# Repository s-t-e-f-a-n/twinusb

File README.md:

# H₂H³ | Twin USB Host Switch × Triple USB Hub (with OLED Telemetry)

**H₂H³** is a compact, STM32 microcontroller-driven USB 2.0 KVM switch and 3-port hub designed to maintain a clean, clutter-free workspace in modern home offices. It enables two computers to seamlessly share a single set of peripherals—like your keyboard, mouse, and flash drives—while delivering live voltage and current telemetry via an integrated OLED display.

> [!NOTE]
> **Project Status & Contribution:** This project is actively developed. The initial commit delivers roughly 90% of the core KVM switching and telemetry functionality in a fully functional prototype stage.
>
> To bring this project to a 100% polished release, **contributions from the open-source community are highly welcome!** Whether you want to optimize edge-case handling in the C++ firmware, implement new USB HID features, or help refine the documentation—feel free to open an issue or submit a Pull Request. Let's build this together!

* **Smart Break-Before-Make Switching:** Advanced, software-controlled VBUS and data line multiplexing ensures safe, glitch-free transitions and isolated power rails between both host PCs.
* **Integrated 3-Port Hub:** Built-in Genesys Logic controller expands a single shared USB connection into three downstream ports for your everyday desk peripherals.
* **🚀 Native Host-MCU Communication (Endless Use Cases!):** Unlike dumb KVM switches, the onboard STM32 MCU is wired directly into the hub as a **fourth USB peripheral device**. This allows the MCU to communicate natively with the active Host PC—opening up vast possibilities for custom PC desktop apps, background telemetry logging, hardware automation scripts, or even full USB HID keyboard/mouse emulation.
* **Live Telemetry Dashboard:** A crisp, integrated 64x32 pixel OLED display provides real-time insights by showing live bus voltage and precise current draw per port.
* **Ergonomic & Screw-less Enclosure:** Features a clean interface with a discreetly placed rear tactile button to prevent cable snags, all housed in a robust, snap-fit PA12-HP Nylon shell optimized for MJF 3D printing.
* **Modern C++ Firmware:** Driven by a powerful STM32G0 architecture running a modular, object-oriented C++ firmware stack with hardware-level overcurrent protection.

🖼️ Jump straight to the [Photo Gallery](#-photo-gallery).

🏪 **Hardware Available:** Skip the assembly line and grab a fully functional H₂H³ on [Tindie](https://www.tindie.com/products/43013/).

## 🔭 Background & Philosophy

H₂H³ represents a personal exploration into modern decentralized manufacturing and open-source engineering. It blends professional design principles with modern open-source software, AI-collaborative programming to refine the C++ firmware, and on-demand fabrication. The fact that an individual engineer can now prototype industrial-grade hardware using low-volume far-east manufacturing is nothing short of incredible.

To give back to the community, the full design files—spanning schematics, mechanics, and source code—are public domain under MIT and CERN Open Hardware licenses. It is intended strictly for educational use, and community-driven remixes are highly encouraged.

## 🛠️ Design Stack & Toolchain

The hardware, enclosure, and software for H₂H³ were designed using the following tools:

* **KiCad 9.0:** Schematic entry and PCB design for the 4-layer board.
* **FreeCAD 1.0:** 3D modeling of the screw-less, snap-fit two-part enclosure.
* **Firmware Toolchain:** Developed in modern modular C++ utilizing **STM32CubeMX** for hardware abstraction. Out of the box, the repository supports a dual-development workflow—you can build and debug the firmware seamlessly using either **Visual Studio Code (via CMake/Ninja)** or **STM32CubeIDE**, depending on your preferred environment.

---

## 🛠️ Hardware Specification

* **Microcontroller:** ARM Cortex-M0+ 32-bit MCU (STM32G0B1KBU6, 64 MHz, 128 KB Flash, 144 KB RAM), integrated as a 4th peripheral on the hub.
* **USB 2.0 Hub Controller:** Genesys Logic GL852G.
* **Physical Interface:** * 2x USB-A Male (Host 1 / Host 2 connections)
  * 3x USB-A Female (Peripheral downstream ports)
* **Telemetry Sensors:** Continuous dual-host VBUS voltage sensing (enables auto-detection) and triple-peripheral current monitoring.
* **Switching Architecture:** Hybrid automatic/software-controlled VBUS muxer combined with hardware USB data line multiplexers.
* **User Interface:** 64x32 pixel OLED screen, 1x rear tactile switch button, and 1x fully programmable RGB LED (color and brightness).
* **Form Factor:** Ultra-compact desktop footprint (approx. 60 × 20 × 20 mm).

<table border="0" style="border: none; border-collapse: collapse;">
  <tr>
    <td style="border: none; padding: 10px;"></td>
    <td style="border: none; padding: 10px;"></td>
    <td style="border: none; padding: 10px;"></td>
  </tr>
</table>

---

## 💻 Software & Firmware Architecture

The firmware is built using **STM32CubeMX** for hardware abstraction and written in **C/C++**.

### Advanced Features

* **Fully Modularized C/C++:** Source code is designed fully modular in C++ with support from the HAL in C automatically created by STM32CubeMX.
* **Optimized ADC Sampling:** Continuous monitoring of port power states with software-side calibration.
* **Overcurrent Detection:** Peripheral current draw of more than 1.5 A enters fault mode which the device resumes from by user confirmation.
* **UART Debug Console:** Retargeted `printf` over the STM32 USART2 or USB virtual COM port.
* **Binary Programming:** Powering on and holding switch button simultaneously enters the programming mode (STM32CubeProgrammer) which enables programming the ST32 integrated flash without the need for a hardware debugger

---

## 📂 Repository Structure

```text
twinusb/
├── assets/                  # Public media & documentation images
├── enclosure/               # Mechanical 3D CAD design (FreeCAD)
├── firmware/                # Production-ready STM32G0 C/C++ firmware
│   ├── App/                 # Core Application Logic (C++)
│   │   ├── Inc/             # Application Managers (Hub, Display, Sensors, UI)
│   │   └── Src/             # Implementation source code
│   ├── Core/                # Hardware peripheral initialization (ADC, I2C, GPIO)
│   ├── cmake/               # Toolchain configuration profiles
│   ├── Libs/                # Embedded drivers & hardware abstraction libraries
│   │   └── oled_waveshare/  # Low-level 0.49" 64x32 OLED display driver components
│   ├── Middlewares/         # STMicroelectronics USB Device Library stack
│   ├── Startup/             # Microcontroller boot vector assembly code
│   └── USB_Device/          # USB CDC Class configuration and descriptor maps
└── hardware/                # Electronics engineering files (KiCad)
    ├── lib_fp/              # Custom PCB footprint libraries (.pretty)
    └── lib_sch/             # Custom schematic component symbols
```

---

## ⚡ Getting Started & Building the Firmware

### 1. Cloning the Repository

```bash
git clone https://github.com/s-t-e-f-a-n/twinusb.git
cd twinusb

```

This project supports a **dual-development workflow**. You can build the firmware using either **VS Code (via CMake)** or the official **STM32CubeIDE**. Choose the workflow that best fits your environment. You do not need to use STM32CubeMX to build the project from scratch.

---

### Method A: Building with VS Code (Recommended)

This method uses CMake and Ninja/Make. It requires a local ARM GCC toolchain installed on your system.

#### Prerequisites

Ensure you have the following installed and available in your system's `PATH`:

* **ARM GNU Toolchain:** `arm-none-eabi-gcc`
* **Build Tools:** `CMake` and `Ninja` (or `Make`)
* **VS Code Extensions:**
* [CMake Tools](https://marketplace.visualstudio.com/items?itemName=ms-vscode.cmake-tools)
* [C/C++ Extension Pack](https://marketplace.visualstudio.com/items?itemName=ms-vscode.cpptools-extension-pack)

#### VS Code Setup & Build Steps

1. **Open Project:** Open the `firmware` directory in VS Code.
2. **Select Compiler Kit:** Open the Command Palette (`Ctrl+Shift+P` / `Cmd+Shift+P`), search for **`CMake: Select a Kit`**, and select your installed `arm-none-eabi` compiler.
3. **Select Build Variant:** Choose either `Debug` or `Release` from the CMake status bar at the bottom.
4. **Configure Project:** Run **`CMake: Configure`** from the Command Palette. This will clean-room generate your local `build/` directory with the correct absolute paths for your machine.
5. **Compile:** Click **`Build`** in the status bar or press `F7`.

---

### Method B: Building with STM32CubeIDE

STM32CubeIDE is an all-in-one Eclipse-based IDE that includes its own compiler toolchain and internal build system out of the box.

#### STM32CubeIDE Setup & Build Steps

1. **Import Project:**

* Open STM32CubeIDE.
* Go to `File` ➔ `Open Projects from Filesystem...`
* Select `Directory` ➔ `Choose twinusb folder` and click *Select Folder*.
* Click *Finish*.

2. **Index Project:** Wait a few moments for the IDE to finish indexing the source files.

3. **Compile:** Click the **Hammer icon (Build)** in the top toolbar, or press `Ctrl+B` (`Cmd+B` on macOS).

---

### ⚠️ Crucial Note on Code Generation (C++ Integration)

The core application logic of this project is written in modern **C++** and lives inside the `App/` directory (`App/Src` and `App/Inc`), keeping it cleanly decoupled from the autogenerated ST HAL layer.

If you decide to open the `twinusb.stm32.ioc` file to modify pinouts or peripherals via STM32CubeMX and click **"Generate Code"**, the tools will reset the project workspace to ST's default pure-C template.

**If your IDE loses track of the C++ files after code generation, fix it manually:**

* **In STM32CubeIDE:** Right-click the project ➔ `Properties` ➔ `C/C++ General` ➔ `Paths and Symbols`.
* Under **Includes**, re-add the `App/Inc` directory.
* Under **Source Location**, re-add the `App/Src` directory.

* **In VS Code:** Simply run **`CMake: Delete Cache and Reconfigure`** from the Command Palette to force CMake to re-scan the file structure.

---

## 🏭 Sourcing the Hardware

### PCB & Assembly

The schematics and PCB layout are located in the `/hardware` folder, designed in KiCad and optimized for automated assembly (PCBA) via services like JLCPCB.

### Enclosure

Print the shell components located in the `/enclosure` folder. Nylon (SLS/MJF technique) is highly recommended for that professional, textured matte finish and mechanical durability.

---

## 📸 Photo Gallery

| &nbsp; | &nbsp; | &nbsp; |
| :---: | :---: | :---: |
|  |  |  |
|  |  |  |
|  |  |  |
|  |  |  |
|  |  |  |
|  |  |  |
|  |  |  |

---

## ⚖️ License

This project is licensed under different Open Source licenses depending on the component:

* 💻 **Firmware & Software:** Licensed under the [MIT License](firmware/LICENSE)
  *(Permissive, commercial-friendly software license)*
* 🔌 **Hardware (PCB & Schematics):** Licensed under the [CERN-OHL-W v2](hardware/LICENSE)
  *(CERN Open Hardware Licence - Weak Copyleft)*
* 📦 **Enclosure (Mechanical CAD):** Licensed under the [CERN-OHL-W v2](enclosure/LICENSE)
  *(CERN Open Hardware Licence - Weak Copyleft)*

All components are copyrighted © 2026 by **s-t-e-f-a-n** who developed them with ❤️

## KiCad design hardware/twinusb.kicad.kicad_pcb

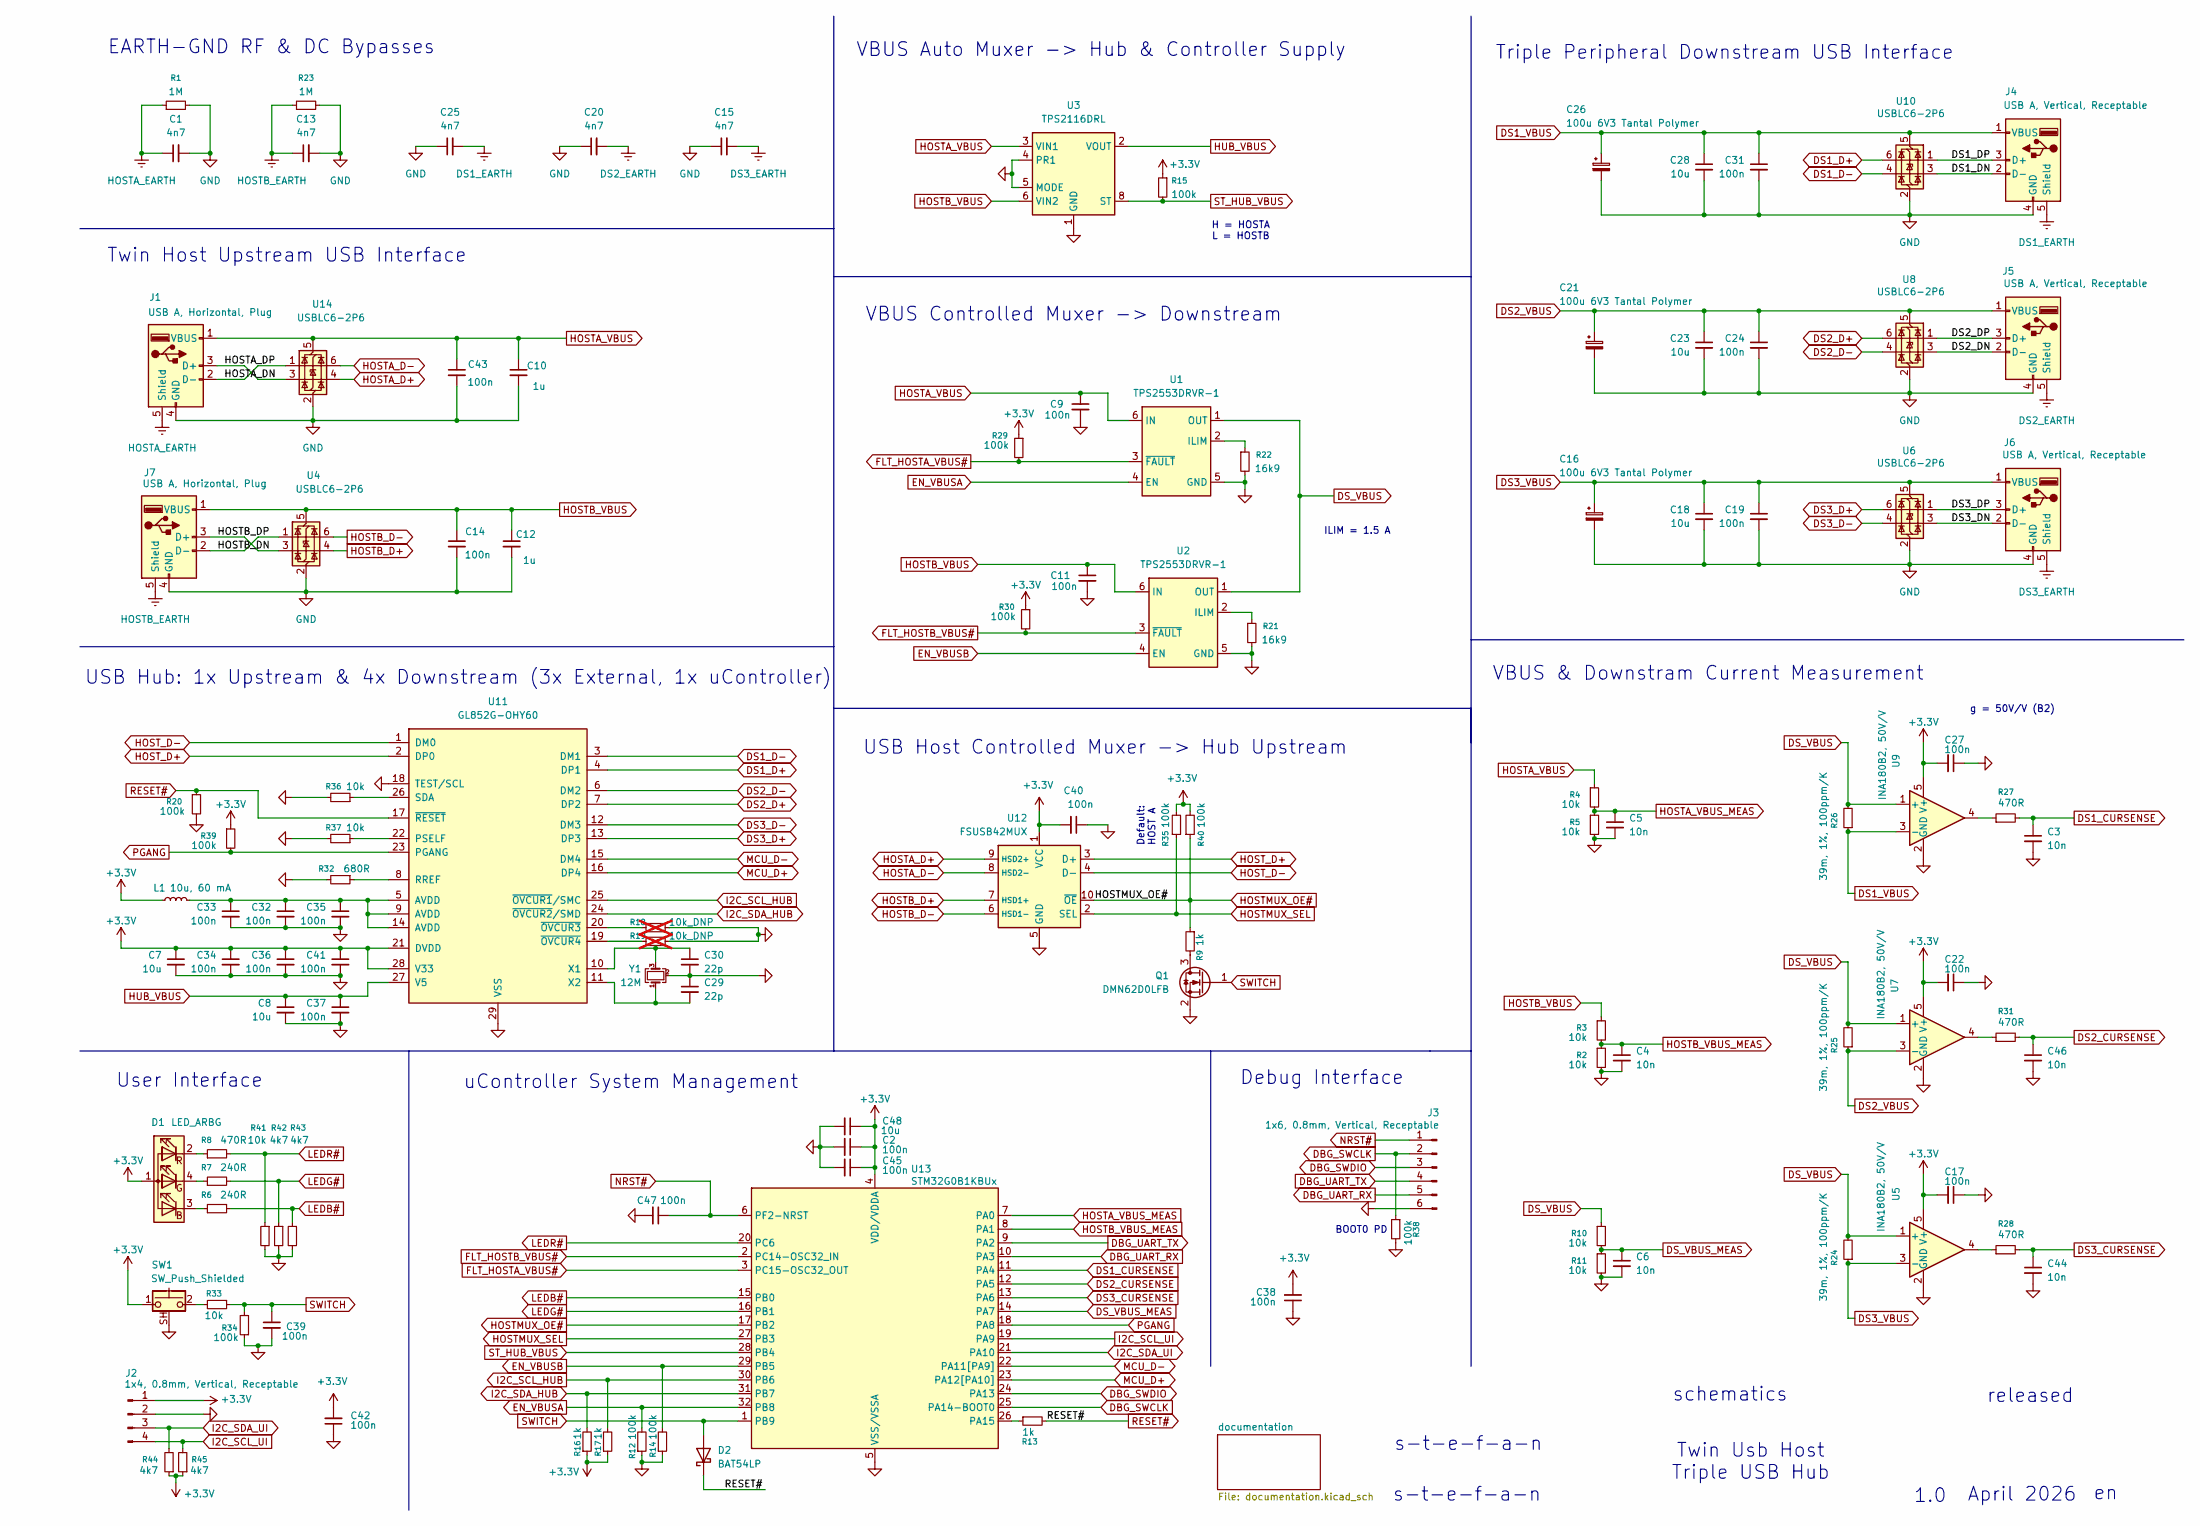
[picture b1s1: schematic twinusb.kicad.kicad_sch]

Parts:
C1, C13, C15, C20, C25: 4n7; C_0603_1608Metric; LCSC PN C85980
C2, C9, C11, C14, C17, C19, C22, C24, C27, C31, C32, C33, C34, C35, C36, C37, C38, C39, C40, C41, C42, C43, C45, C47: 100n; C_0402_1005Metric; LCSC PN C307331
C3, C4, C5, C6, C44, C46: 10n; C_0402_1005Metric; LCSC PN C15195
C7, C8, C18, C23, C28, C48: 10u; C_0603_1608Metric; LCSC PN C19702
C10, C12: 1u; C_0402_1005Metric; LCSC PN C52923
C16, C21, C26: 100u 6V3 Tantal Polymer; CP_EIA-3216-18_Kemet-A; MPN T520A107M006ATE070; LCSC PN C561794
C29, C30: 22p; C_0402_1005Metric; LCSC PN C1555
D1: LED_ARBG; LED_RGB_Kingbright_APHF1608LSEEQBDZGKC; MPN APHF1608LSEEQBDZGKC; LCSC PN C3019171
D2: BAT54LP; Diodes_DFN1006-2; MPN BAT54LP; LCSC PN C134410
J1, J7: USB A, Horizontal, Plug; USB_A_Horizontal_THT; MPN UP2-AH-1-TH; Mouser PN 490-UP2-AH-1-TH
J2: 1x4, 0.8mm, Vertical, Receptable; JST_SUR_BM04B-SURS-TF_1x04-1MP_P0.80mm_Vertical; MPN BM04B-SURS-TF; LCSC PN C495551
J3: 1x6, 0.8mm, Vertical, Receptable; JST_SUR_BM06B-SURS-TF_1x06-1MP_P0.80mm_Vertical; MPN BM06B-SURS-TF; LCSC PN C5118712
J4, J5, J6: USB A, Vertical, Receptable; USB_A_Vertical_AMPHENOL_UE27AE54100; MPN UE27-AE54-100; Mouser PN 523-UE27-AE54-100
L1: 10u, 60 mA; L_0603_1608Metric; MPN MLZ1608N100LTD25; LCSC PN C307750
Q1: DMN62D0LFB; DFN1006-3; MPN DMN62D0LFB; LCSC PN C397945
R1, R23: 1M; R_0402_1005Metric; LCSC PN C26083
R2, R3, R4, R5, R10, R11, R33, R36, R37, R41: 10k; R_0402_1005Metric; LCSC PN C60490
R6, R7: 240R; R_0402_1005Metric; LCSC PN C114755
R8, R27, R28, R31: 470R; R_0402_1005Metric; LCSC PN C25117
R9, R13, R16, R17: 1k; R_0402_1005Metric; LCSC PN C11702
R12, R14, R15, R20, R29, R30, R34, R35, R38, R39, R40: 100k; R_0402_1005Metric; LCSC PN C25741
R18, R19: 10k_DNP; R_0402_1005Metric; LCSC PN C60490; not fitted
R21, R22: 16k9; R_0402_1005Metric; LCSC PN C25858
R24, R25, R26: 39m, 1%, 100ppm/K; R_0603_1608Metric; MPN PE0603FRF7T0R039L; LCSC PN C858571
R32: 680R; R_0402_1005Metric; LCSC PN C25130
R42, R43, R44, R45: 4k7; R_0402_1005Metric; LCSC PN C25900
SW1: SW_Push_Shielded; SW_Tactile_SPST_Angled_PTS645Vx58-2LFS; MPN PTS645VH58-2 LFS; Mouser PN 611-PTS645VH582
U1, U2: TPS2553DRVR-1; WSON-6-1EP_2x2mm_P0.65mm_EP1x1.6mm_ThermalVias; MPN TPS2553DRVR-1; LCSC PN C411878
U3: TPS2116DRL; SOT-583-8; MPN TPS2116DRLR; LCSC PN C3235557
U4, U6, U8, U10, U14: USBLC6-2P6; SOT-666; MPN USBLC6-2P6; LCSC PN C15999
U5, U7, U9: INA180B2, 50V/V; SOT-23-5; MPN INA180B2IDBVR; LCSC PN C2861539
U11: GL852G-OHY60; QFN-28-1EP_5x5mm_P0.5mm_EP3.75x3.75mm_ThermalVias; MPN GL852G-OHY60; LCSC PN C7501404
U12: FSUSB42MUX; MSOP-10_3x3mm_P0.5mm; MPN FSUSB42MUX; LCSC PN C11355
U13: STM32G0B1KBUx; QFN-32-1EP_5x5mm_P0.5mm_EP3.45x3.45mm_ThermalVias; MPN STM32G0B1KBU6; LCSC PN C5159549
Y1: 12M; Crystal_SMD_3225-4Pin_3.2x2.5mm; MPN X322512MSB4SI; LCSC PN C9002

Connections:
+3.3V: C2.1, C7.1, C17.2, C22.2, C27.2, C34.1, C36.1, C38.2, C40.2, C41.1, C42.2, C45.1, C48.1, D1.1 (A), J2.1, L1.1, R15.1, R16.1, R17.1, R29.1, R30.1, R35.2, R39.1, R40.2, R44.1, R45.1, SW1.1, U5.5 (V+), U7.5 (V+), U9.5 (V+), U11.21 (DVDD), U11.28 (V33), U12.1 (VCC), U13.4 (VDD/VDDA)
/DS1_DN: J4.2 (D-), U10.3 (I/O2)
/DS1_DP: J4.3 (D+), U10.1 (I/O1)
/DS2_DN: J5.2 (D-), U8.3 (I/O2)
/DS2_DP: J5.3 (D+), U8.1 (I/O1)
/DS3_DN: J6.2 (D-), U6.3 (I/O2)
/DS3_DP: J6.3 (D+), U6.1 (I/O1)
/HOSTA_DN: J1.2 (D-), U14.1 (I/O1)
/HOSTA_DP: J1.3 (D+), U14.3 (I/O2)
/HOSTB_DN: J7.2 (D-), U4.1 (I/O1)
/HOSTB_DP: J7.3 (D+), U4.3 (I/O2)
DBG_SWCLK: J3.2, R38.1, U13.25 (PA14-BOOT0)
DBG_SWDIO: J3.3, U13.24 (PA13)
DBG_UART_RX: J3.5, U13.10 (PA3)
DBG_UART_TX: J3.4, U13.9 (PA2)
DS1_CURSENSE: C3.1, R27.2, U13.11 (PA4)
DS1_D+: U10.6 (I/O1), U11.4 (DP1)
DS1_D-: U10.4 (I/O2), U11.3 (DM1)
DS1_EARTH: C25.2, J4.5 (Shield)
DS1_VBUS: C26.1, C28.1, C31.1, J4.1 (VBUS), R26.1, U9.3 (-), U10.5 (VBUS)
DS2_CURSENSE: C46.1, R31.2, U13.12 (PA5)
DS2_D+: U8.6 (I/O1), U11.7 (DP2)
DS2_D-: U8.4 (I/O2), U11.6 (DM2)
DS2_EARTH: C20.2, J5.5 (Shield)
DS2_VBUS: C21.1, C23.1, C24.1, J5.1 (VBUS), R25.1, U7.3 (-), U8.5 (VBUS)
DS3_CURSENSE: C44.1, R28.2, U13.13 (PA6)
DS3_D+: U6.6 (I/O1), U11.13 (DP3)
DS3_D-: U6.4 (I/O2), U11.12 (DM3)
DS3_EARTH: C15.2, J6.5 (Shield)
DS3_VBUS: C16.1, C18.1, C19.1, J6.1 (VBUS), R24.1, U5.3 (-), U6.5 (VBUS)
DS_VBUS: R10.1, R24.2, R25.2, R26.2, U1.1 (OUT), U2.1 (OUT), U5.1 (+), U7.1 (+), U9.1 (+)
DS_VBUS_MEAS: C6.1, R10.2, R11.1, U13.14 (PA7)
EN_VBUSA: R12.2, U1.4 (EN), U13.32 (PB8)
EN_VBUSB: R14.2, U2.4 (EN), U13.29 (PB5)
FLT_HOSTA_VBUS#: R29.2, U1.3 (~FAULT), U13.3 (PC15-OSC32_OUT)
FLT_HOSTB_VBUS#: R30.2, U2.3 (~FAULT), U13.2 (PC14-OSC32_IN)
GND: C1.2, C2.2, C3.2, C4.2, C5.2, C6.2, C7.2, C8.2, C9.2, C10.2, C11.2, C12.2, C13.2, C14.2, C15.1, C16.2, C17.1, C18.2, C19.2, C20.1, C21.2, C22.1, C23.2, C24.2, C25.1, C26.2, C27.1, C28.2, C29.1, C30.2, C31.2, C32.2, C33.2, C34.2, C35.2, C36.2, C37.2, C38.1, C39.2, C40.1, C41.2, C42.1, C43.2, C44.2, C45.2, C46.2, C47.2, C48.2, J1.4 (GND), J2.2, J3.6, J4.4 (GND), J5.4 (GND), J6.4 (GND), J7.4 (GND), Q1.2 (S), R1.2, R2.2, R5.2, R11.2, R12.1, R14.1, R18.1, R19.1, R20.2, R21.2, R22.2, R23.2, R32.2, R34.1, R36.2, R37.2, R38.2, R41.2, R42.2, R43.2, SW1.SH (B), U1.5 (GND), U1.7 (TP), U2.5 (GND), U2.7 (TP), U3.1 (GND), U3.4 (PR1), U3.5 (MODE), U4.2 (GND), U5.2 (GND), U6.2 (GND), U7.2 (GND), U8.2 (GND), U9.2 (GND), U10.2 (GND), U11.18 (TEST/SCL), U11.29 (VSS), U12.5 (GND), U13.5 (VSS/VSSA), U13.33 (VSS), U14.2 (GND), Y1.2 (G), Y1.4 (G)
HOSTA_D+: U12.9 (HSD2+), U14.4 (I/O2)
HOSTA_D-: U12.8 (HSD2-), U14.6 (I/O1)
HOSTA_EARTH: C1.1, J1.5 (Shield), R1.1
HOSTA_VBUS: C9.1, C10.1, C43.1, J1.1 (VBUS), R4.1, U1.6 (IN), U3.3 (VIN1), U14.5 (VBUS)
HOSTA_VBUS_MEAS: C5.1, R4.2, R5.1, U13.7 (PA0)
HOSTB_D+: U4.4 (I/O2), U12.7 (HSD1+)
HOSTB_D-: U4.6 (I/O1), U12.6 (HSD1-)
HOSTB_EARTH: C13.1, J7.5 (Shield), R23.1
HOSTB_VBUS: C11.1, C12.1, C14.1, J7.1 (VBUS), R3.1, U2.6 (IN), U3.6 (VIN2), U4.5 (VBUS)
HOSTB_VBUS_MEAS: C4.1, R2.1, R3.2, U13.8 (PA1)
HOSTMUX_OE#: R9.1, R40.1, U12.10 (~OE), U13.17 (PB2)
HOSTMUX_SEL: R35.1, U12.2 (SEL), U13.27 (PB3)
HOST_D+: U11.2 (DP0), U12.3 (D+)
HOST_D-: U11.1 (DM0), U12.4 (D-)
HUB_VBUS: C8.1, C37.1, U3.2 (VOUT), U3.7 (VOUT), U11.27 (V5)
I2C_SCL_HUB: R17.2, U11.25 (~OVCUR1/SMC), U13.30 (PB6)
I2C_SCL_UI: J2.4, R45.2, U13.19 (PA9)
I2C_SDA_HUB: R16.2, U11.24 (~OVCUR2/SMD), U13.31 (PB7)
I2C_SDA_UI: J2.3, R44.2, U13.21 (PA10)
LEDB#: R6.2, R43.1, U13.15 (PB0)
LEDG#: R7.2, R42.1, U13.16 (PB1)
LEDR#: R8.2, R41.1, U13.20 (PC6)
MCU_D+: U11.16 (DP4), U13.23 (PA12[PA10])
MCU_D-: U11.15 (DM4), U13.22 (PA11[PA9])
NRST#: C47.1, J3.1, U13.6 (PF2-NRST)
unnamed: C32.1, C33.1, C35.1, L1.2, U11.5 (AVDD), U11.9 (AVDD), U11.14 (AVDD)
unnamed: D1.3 (BK), R6.1
unnamed: D1.4 (GK), R7.1
unnamed: D1.2 (RK), R8.1
unnamed: Q1.3 (D), R9.2
unnamed: R27.1, U9.4
unnamed: R28.1, U5.4
unnamed: R31.1, U7.4
unnamed: R33.2, SW1.2
unnamed: R22.1, U1.2 (ILIM)
unnamed: R21.1, U2.2 (ILIM)
unnamed: R37.1, U11.22 (PSELF)
unnamed: R32.1, U11.8 (RREF)
unnamed: R36.1, U11.26 (SDA)
unnamed: C30.1, U11.10 (X1), Y1.3
unnamed: C29.2, U11.11 (X2), Y1.1
unnamed: R18.2, U11.20 (~OVCUR3)
unnamed: R19.2, U11.19 (~OVCUR4)
unnamed: R13.1, U13.26 (PA15)
PGANG: R39.2, U11.23 (PGANG), U13.18 (PA8)
RESET#: D2.1 (K), R13.2, R20.1, U11.17 (~RESET)
ST_HUB_VBUS: R15.2, U3.8 (ST), U13.28 (PB4)
SWITCH: C39.1, D2.2 (A), Q1.1 (G), R33.1, R34.2, U13.1 (PB9)

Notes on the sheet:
ILIM = 1.5 A
s-t-e-f-a-n
USB Host Controlled Muxer -> Hub Upstream
Triple Peripheral Downstream USB Interface
1.0
schematics
BOOT0 PD
H = HOSTA L = HOSTB
VBUS & Downstram Current Measurement
VBUS Auto Muxer -> Hub & Controller Supply
April 2026
User Interface
EARTH-GND RF & DC Bypasses
Twin Host Upstream USB Interface
uController System Management
Default: HOST A
Debug Interface
Twin Usb Host Triple USB Hub
USB Hub: 1x Upstream & 4x Downstream (3x External, 1x uController)
VBUS Controlled Muxer -> Downstream
released
g = 50V/V (B2)

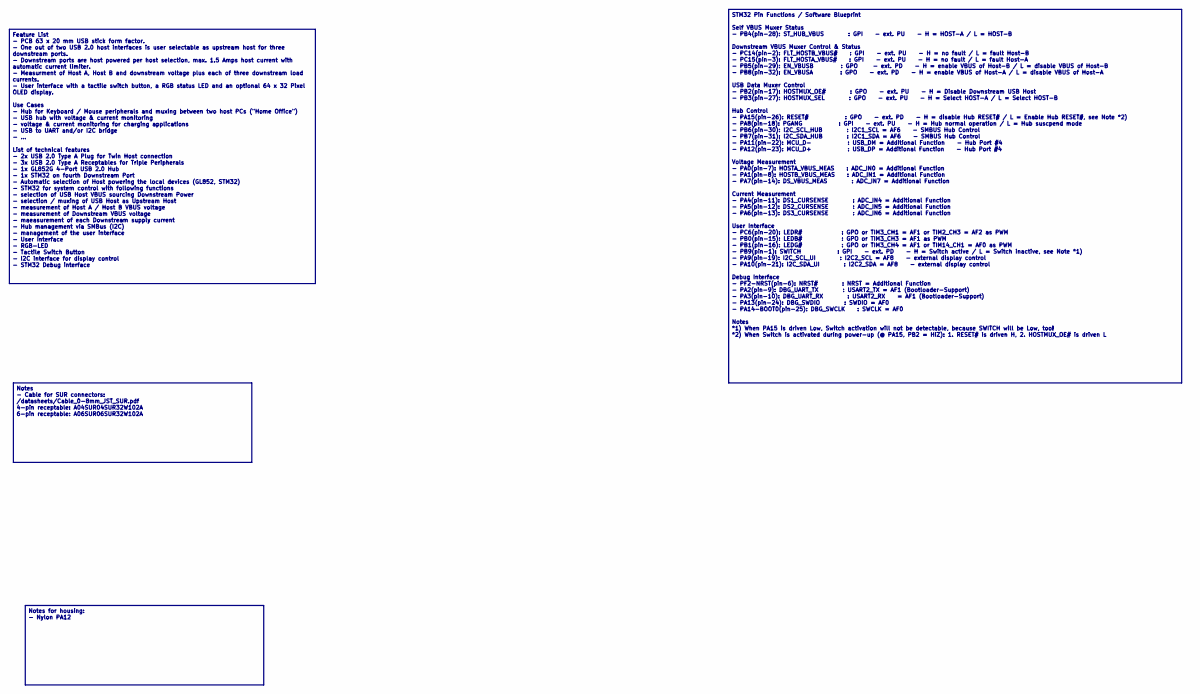
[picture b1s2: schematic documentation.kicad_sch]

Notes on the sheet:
Notes - Cable for SUR connectors: /datasheets/Cable_0-8mm_JST_SUR.pdf 4-pin receptable: A04SUR04SUR32W102A 6-pin receptable: A06SUR06SUR32W102A
STM32 Pin Functions / Software Blueprint Self VBUS Muxer Status - PB4(pin-28): ST_HUB_VBUS : GPI - ext. PU - H = HOST-A / L = HOST-B Downstream VBUS Muxer Control & Status - PC14(pin-2): FLT_HOSTB_VBUS# : GPI - ext. PU - H = no fault / L = fault Host-B - PC15(pin-3): FLT_HOSTA_VBUS# : GPI - ext. PU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
Feature List - PCB 63 x 20 mm USB stick form factor. - One out of two USB 2.0 host interfaces is user selectable as upstream host for three downstream ports. - Downstream ports are host powered per host selection, max. 1.5 Amps host current with automatic current limiter. - Measurment of Host A, Ho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
Notes for housing: - Nylon PA12

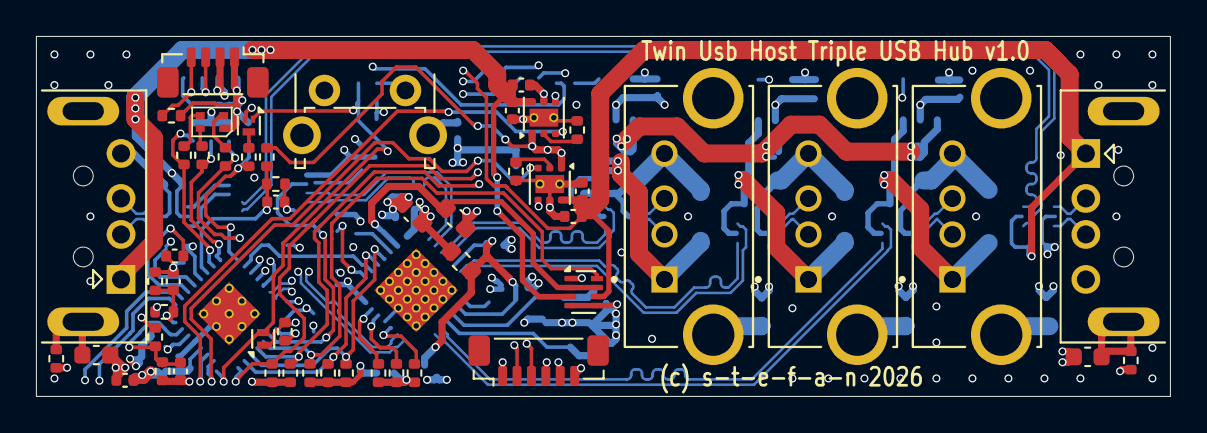
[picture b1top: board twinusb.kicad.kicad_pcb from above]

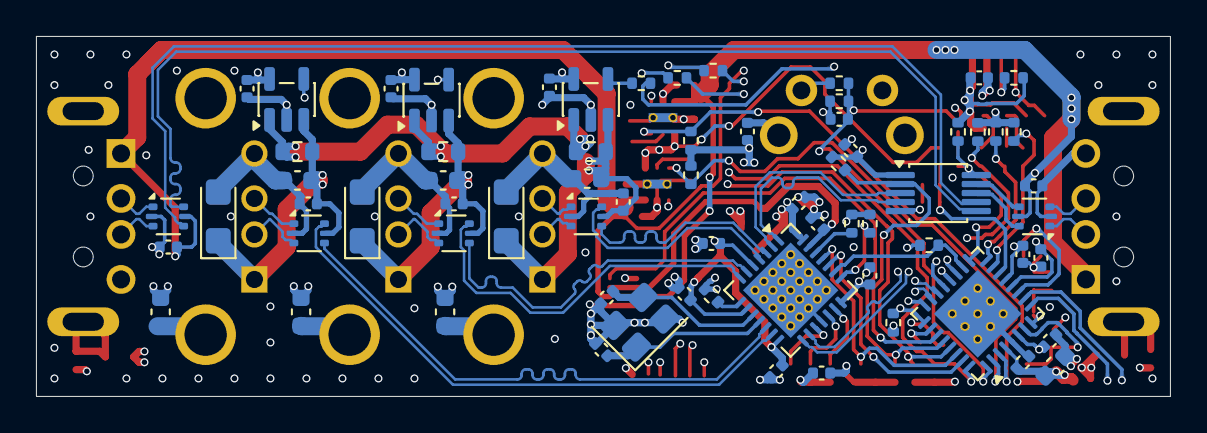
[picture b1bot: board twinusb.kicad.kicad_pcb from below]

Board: 4 copper layers, 63.0 x 20.0 mm, 120 parts (68 on the bottom side), 85 nets.

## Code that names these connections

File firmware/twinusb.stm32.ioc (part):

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Mcu.Name=STM32G0B1K(B-C-E)Ux
Mcu.Package=UFQFPN32
Mcu.UserName=STM32G0B1KBUx
PA0.GPIOParameters=GPIO_Label
PA0.GPIO_Label=HOSTA_VBUS_MEAS
PA0.Mode=IN0
PA0.Signal=ADC1_IN0
PA1.GPIOParameters=GPIO_Label
PA1.GPIO_Label=HOSTB_VBUS_MEAS
PA1.Mode=IN1
PA1.Signal=ADC1_IN1
PA10.GPIOParameters=GPIO_Label
PA10.GPIO_Label=I2C_SDA_UI
PA10.Mode=I2C
PA10.Signal=I2C2_SDA
PA11\ [PA9].GPIOParameters=GPIO_Label
PA11\ [PA9].GPIO_Label=MCU_DM
PA11\ [PA9].Mode=Device
PA11\ [PA9].Signal=USB_DM
PA12\ [PA10].GPIOParameters=GPIO_Label
PA12\ [PA10].GPIO_Label=MCU_DP
PA12\ [PA10].Mode=Device
PA12\ [PA10].Signal=USB_DP
PA13.Mode=Serial_Wire
PA13.Signal=SYS_SWDIO
PA14-BOOT0.Mode=Serial_Wire
PA14-BOOT0.Signal=SYS_SWCLK
PA15.GPIOParameters=GPIO_Label
PA15.GPIO_Label=RESETn
PA15.Signal=GPIO_Output
PA2.Mode=Asynchronous
PA2.Signal=USART2_TX
PA3.Mode=Asynchronous
PA3.Signal=USART2_RX
PA4.GPIOParameters=GPIO_Label
PA4.GPIO_Label=DS1_CURSENSE
PA4.Mode=IN4
PA4.Signal=ADC1_IN4
PA5.GPIOParameters=GPIO_Label
PA5.GPIO_Label=DS2_CURSENSE
PA5.Mode=IN5
PA5.Signal=ADC1_IN5
PA6.GPIOParameters=GPIO_Label
PA6.GPIO_Label=DS3_CURSENSE
PA6.Mode=IN6
PA6.Signal=ADC1_IN6
PA7.GPIOParameters=GPIO_Label
PA7.GPIO_Label=DS_VBUS_MEAS
PA7.Mode=IN7
PA7.Signal=ADC1_IN7
PA8.GPIOParameters=GPIO_Label
PA8.GPIO_Label=PGANG
PA8.Signal=GPIO_Input
PA9.GPIOParameters=GPIO_Label
PA9.GPIO_Label=I2C_SCL_UI
PA9.Mode=I2C
PA9.Signal=I2C2_SCL
PB0.GPIOParameters=GPIO_Label
PB0.GPIO_Label=LEDBn
PB0.Signal=S_TIM3_CH3
PB1.GPIOParameters=GPIO_Label
PB1.GPIO_Label=LEDGn
PB1.Signal=S_TIM3_CH4
PB2.GPIOParameters=GPIO_Label
PB2.GPIO_Label=HOSTMUX_OEn
PB2.Signal=GPIO_Output
PB3.GPIOParameters=GPIO_Label
PB3.GPIO_Label=HOSTMUX_SEL
PB3.Signal=GPIO_Output
PB4.GPIOParameters=GPIO_Label
PB4.GPIO_Label=ST_HUB_VBUS
PB4.Signal=GPIO_Input
PB5.GPIOParameters=GPIO_Label
PB5.GPIO_Label=EN_VBUSB
PB5.Signal=GPIO_Output
PB6.GPIOParameters=GPIO_Speed,GPIO_Pu,GPIO_Mode
PB6.GPIO_Mode=GPIO_MODE_AF_OD
PB6.GPIO_Pu=GPIO_NOPULL
PB6.GPIO_Speed=GPIO_SPEED_FREQ_LOW
PB6.Mode=I2C
PB6.Signal=I2C1_SCL
PB7.GPIOParameters=GPIO_Speed,GPIO_Pu,GPIO_Mode
PB7.GPIO_Mode=GPIO_MODE_AF_OD
PB7.GPIO_Pu=GPIO_NOPULL
PB7.GPIO_Speed=GPIO_SPEED_FREQ_LOW
PB7.Mode=I2C
PB7.Signal=I2C1_SDA
PB8.GPIOParameters=GPIO_Label
PB8.GPIO_Label=EN_VBUSA
PB8.Signal=GPIO_Output
PB9.GPIOParameters=GPIO_Label,GPIO_ModeDefaultEXTI
PB9.GPIO_Label=SWITCH
PB9.GPIO_ModeDefaultEXTI=GPIO_MODE_IT_RISING_FALLING
PB9.Signal=GPXTI9
PC14-OSC32_IN\ (PC14).GPIOParameters=GPIO_Label
PC14-OSC32_IN\ (PC14).GPIO_Label=FLT_HOSTB_VBUSn
PC14-OSC32_IN\ (PC14).Signal=GPIO_Input
PC15-OSC32_OUT\ (PC15).GPIOParameters=GPIO_Label
PC15-OSC32_OUT\ (PC15).GPIO_Label=FLT_HOSTA_VBUSn
PC15-OSC32_OUT\ (PC15).Signal=GPIO_Input
PC6.GPIOParameters=GPIO_Label
PC6.GPIO_Label=LEDRn
PC6.Signal=S_TIM3_CH1
RCC.HSE_VALUE=8000000
RCC.SYSCLKFreq_VALUE=64000000
RCC.SYSCLKSource=RCC_SYSCLKSOURCE_PLLCLK
board=custom

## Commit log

2026-06-23 feat: initial release of twinusb hardware, firmware, and enclosure
2026-06-24 doc: README.md update
2026-06-27 fix: state machine couldn't handle overload fault correctly fix: host disconnection was not correctly reflected on status header/footer line feat: ADC calibration and sensor value filtering added fea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
2026-06-29 doc: more photos, movies and hardware blockdiagram
2026-06-30 doc: added some assets
